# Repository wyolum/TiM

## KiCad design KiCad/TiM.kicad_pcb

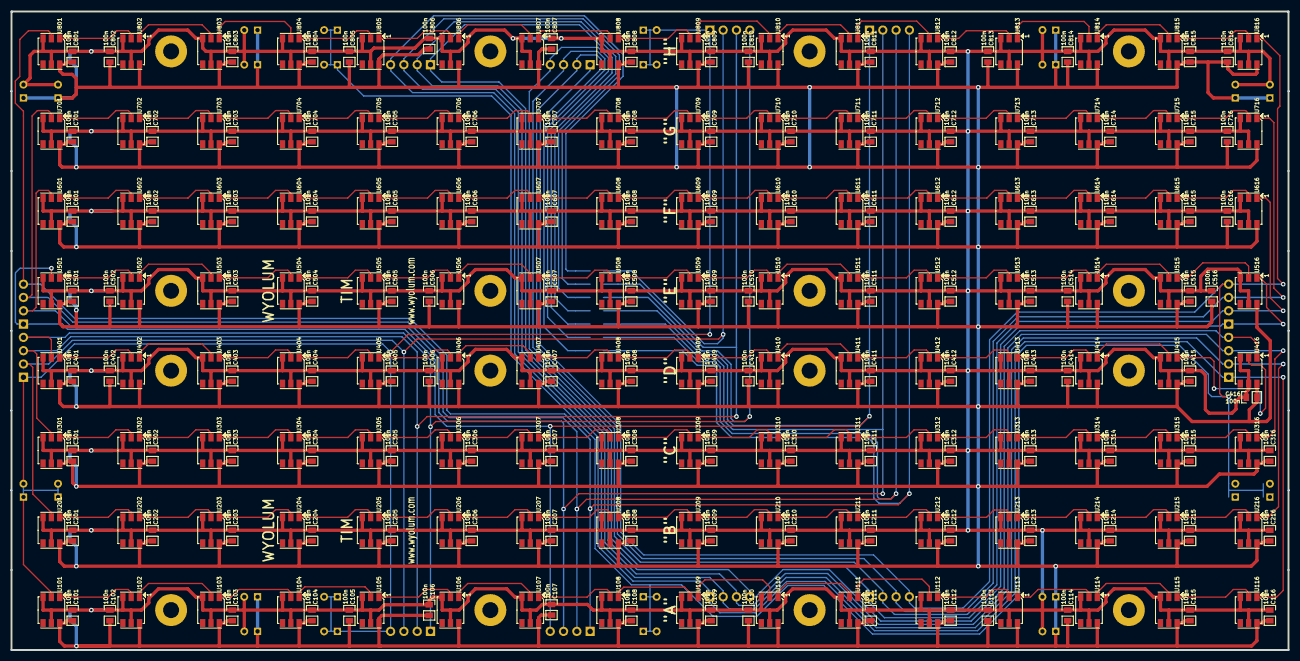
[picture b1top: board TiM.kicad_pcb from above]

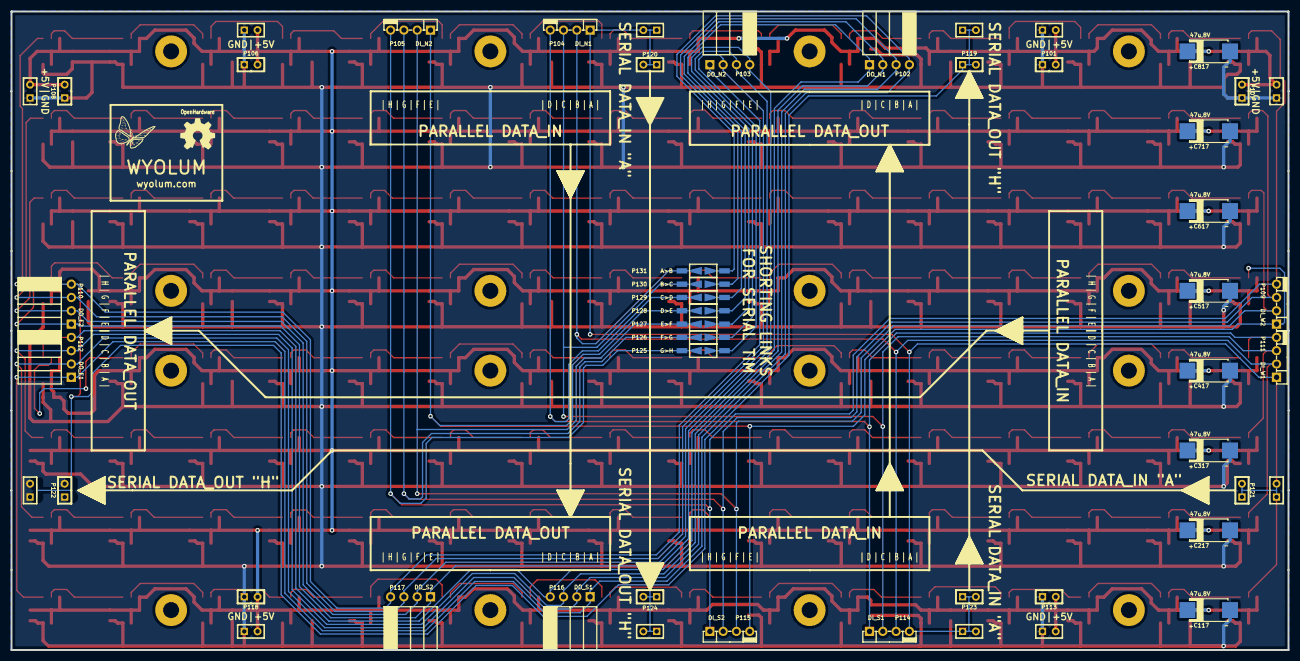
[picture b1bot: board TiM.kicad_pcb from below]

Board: 2 copper layers, 243.8 x 121.9 mm, 313 parts (41 on the bottom side), 138 nets.

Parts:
C101, C102, C103, C104, C105, C106, C107, C108, C109, C110, C111, C112, C113, C114, C115, C116, C201, C202, C203, C204, C205, C206, C207, C208, C209, C210, C211, C212, C213, C214, C215, C216, C301, C302, C303, C304, C305, C306, C307, C308, C309, C310, C311, C312, C313, C314, C315, C316, C401, C402, C403, C404, C405, C406, C407, C408, C409, C410, C411, C412, C413, C414, C415, C416, C501, C502, C503, C504, C505, C506, C507, C508, C509, C510, C511, C512, C513, C514, C515, C516, C601, C602, C603, C604, C605, C606, C607, C608, C609, C610, C611, C612, C613, C614, C615, C616, C701, C702, C703, C704, C705, C706, C707, C708, C709, C710, C711, C712, C713, C714, C715, C716, C801, C802, C803, C804, C805, C806, C807, C808, C809, C810, C811, C812, C813, C814, C815, C816: 100n; c_0805
C117, C217, C317, C417, C517, C617, C717, C817: 47u,8V; c_2917
L101: OSHW; OSHW_6mm
L102: Wyolum; Logo-WL3
P101: PWR_NW; SIL-PWR-2
P102: DO_N1; CONN_S
P103: DO_N2; CONN_S
P104: DI_N1; CONN_N
P105: DI_N2; CONN_N
P106: PWR_NE; SIL-PWR-2
P107: PWR_W; SIL-PWR
P108: PWR_E; SIL-PWR-2
P109: DI_W2; CONN_N
P110: DO_E2; CONN_S
P111: DI_W1; CONN_N
P112: DO_E1; CONN_S
P113: PWR_SW; SIL-PWR
P114: DI_S1; CONN_N
P115: DI_S2; CONN_N
P116: DO_S1; CONN_S
P117: DO_S2; CONN_S
P118: PWR_SE; SIL-PWR
P119, P122: DO_H_SER; SIL-PWR-2
P120, P121: DI_A_SER; SIL-PWR
P123: DI_A_Ser; SIL-PWR
P124: DO_H_Ser; SIL-PWR-2
P125: G>H; ShortLink2
P126: F>G; ShortLink2
P127: E>F; ShortLink2
P128: D>E; ShortLink2
P129: C>D; ShortLink2
P130: B>C; ShortLink2
P131: A>B; ShortLink2
S101, S102, S103, S104, S401, S402, S403, S404, S501, S502, S503, S504, S801, S802, S803, S804: CONN_1; Screw
U101, U102, U103, U104, U105, U106, U107, U108, U109, U110, U111, U112, U113, U114, U115, U116, U201, U202, U203, U204, U205, U206, U207, U208, U209, U210, U211, U212, U213, U214, U215, U216, U301, U302, U303, U304, U305, U306, U307, U308, U309, U310, U311, U312, U313, U314, U315, U316, U401, U402, U403, U404, U405, U406, U407, U408, U409, U410, U411, U412, U413, U414, U415, U416, U501, U502, U503, U504, U505, U506, U507, U508, U509, U510, U511, U512, U513, U514, U515, U516, U601, U602, U603, U604, U605, U606, U607, U608, U609, U610, U611, U612, U613, U614, U615, U616, U701, U702, U703, U704, U705, U706, U707, U708, U709, U710, U711, U712, U713, U714, U715, U716, U801, U802, U803, U804, U805, U806, U807, U808, U809, U810, U811, U812, U813, U814, U815, U816: RGB_WS2811

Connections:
5V: C101.2, C102.2, C103.2, C104.2, C105.2, C106.2, C107.2, C108.2, C109.2, C110.2, C111.2, C112.2, C113.2, C114.2, C115.2, C116.2, C117.1, C201.2, C202.2, C203.2, C204.2, C205.2, C206.2, C207.2, C208.2, C209.2, C210.2, C211.2, C212.2, C213.2, C214.2, C215.2, C216.2, C217.1, C301.2, C302.2, C303.2, C304.2, C305.2, C306.2, C307.2, C308.2, C309.2, C310.2, C311.2, C312.2, C313.2, C314.2, C315.2, C316.2, C317.1, C401.2, C402.2, C403.2, C404.2, C405.2, C406.2, C407.2, C408.2, C409.2, C410.2, C411.2, C412.2, C413.2, C414.2, C415.2, C416.2, C417.1, C501.2, C502.2, C503.2, C504.2, C505.2, C506.2, C507.2, C508.2, C509.2, C510.2, C511.2, C512.2, C513.2, C514.2, C515.2, C516.2, C517.1, C601.2, C602.2, C603.2, C604.2, C605.2, C606.2, C607.2, C608.2, C609.2, C610.2, C611.2, C612.2, C613.2, C614.2, C615.2, C616.2, C617.1, C701.2, C702.2, C703.2, C704.2, C705.2, C706.2, C707.2, C708.2, C709.2, C710.2, C711.2, C712.2, C713.2, C714.2, C715.2, C716.2, C717.1, C801.2, C802.2, C803.2, C804.2, C805.2, C806.2, C807.2, C808.2, C809.2, C810.2, C811.2, C812.2, C813.2, C814.2, C815.2, C816.2, C817.1, P101.1, P106.1, P107.1, P108.1, P113.1, P118.1, U101.3, U101.5, U102.3, U102.5, U103.3, U103.5, U104.3, U104.5, U105.3, U105.5, U106.3, U106.5, U107.3, U107.5, U108.3, U108.5, U109.3, U109.5, U110.3, U110.5, U111.3, U111.5, U112.3, U112.5, U113.3, U113.5, U114.3, U114.5, U115.3, U115.5, U116.3, U116.5, U201.3, U201.5, U202.3, U202.5, U203.3, U203.5, U204.3, U204.5, U205.3, U205.5, U206.3, U206.5, U207.3, U207.5, U208.3, U208.5, U209.3, U209.5, U210.3, U210.5, U211.3, U211.5, U212.3, U212.5, U213.3, U213.5, U214.3, U214.5, U215.3, U215.5, U216.3, U216.5, U301.3, U301.5, U302.3, U302.5, U303.3, U303.5, U304.3, U304.5, U305.3, U305.5, U306.3, U306.5, U307.3, U307.5, U308.3, U308.5, U309.3, U309.5, U310.3, U310.5, U311.3, U311.5, U312.3, U312.5, U313.3, U313.5, U314.3, U314.5, U315.3, U315.5, U316.3, U316.5, U401.3, U401.5, U402.3, U402.5, U403.3, U403.5, U404.3, U404.5, U405.3, U405.5, U406.3, U406.5, U407.3, U407.5, U408.3, U408.5, U409.3, U409.5, U410.3, U410.5, U411.3, U411.5, U412.3, U412.5, U413.3, U413.5, U414.3, U414.5, U415.3, U415.5, U416.3, U416.5, U501.3, U501.5, U502.3, U502.5, U503.3, U503.5, U504.3, U504.5, U505.3, U505.5, U506.3, U506.5, U507.3, U507.5, U508.3, U508.5, U509.3, U509.5, U510.3, U510.5, U511.3, U511.5, U512.3, U512.5, U513.3, U513.5, U514.3, U514.5, U515.3, U515.5, U516.3, U516.5, U601.3, U601.5, U602.3, U602.5, U603.3, U603.5, U604.3, U604.5, U605.3, U605.5, U606.3, U606.5, U607.3, U607.5, U608.3, U608.5, U609.3, U609.5, U610.3, U610.5, U611.3, U611.5, U612.3, U612.5, U613.3, U613.5, U614.3, U614.5, U615.3, U615.5, U616.3, U616.5, U701.3, U701.5, U702.3, U702.5, U703.3, U703.5, U704.3, U704.5, U705.3, U705.5, U706.3, U706.5, U707.3, U707.5, U708.3, U708.5, U709.3, U709.5, U710.3, U710.5, U711.3, U711.5, U712.3, U712.5, U713.3, U713.5, U714.3, U714.5, U715.3, U715.5, U716.3, U716.5, U801.3, U801.5, U802.3, U802.5, U803.3, U803.5, U804.3, U804.5, U805.3, U805.5, U806.3, U806.5, U807.3, U807.5, U808.3, U808.5, U809.3, U809.5, U810.3, U810.5, U811.3, U811.5, U812.3, U812.5, U813.3, U813.5, U814.3, U814.5, U815.3, U815.5, U816.3, U816.5
/Row_A/A_02: U101.1, U102.2
/Row_A/A_03: U102.1, U103.2
/Row_A/A_04: U103.1, U104.2
/Row_A/A_05: U104.1, U105.2
/Row_A/A_06: U105.1, U106.2
/Row_A/A_07: U106.1, U107.2
/Row_A/A_08: U107.1, U108.2
/Row_A/A_09: U108.1, U109.2
/Row_A/A_10: U109.1, U110.2
/Row_A/A_11: U110.1, U111.2
/Row_A/A_12: U111.1, U112.2
/Row_A/A_13: U112.1, U113.2
/Row_A/A_14: U113.1, U114.2
/Row_A/A_15: U114.1, U115.2
/Row_A/A_16: U115.1, U116.2
/Row_A/DI_A: P104.4, P111.4, P114.1, P120.1, P120.2, P121.1, P121.2, P123.1, P123.2, U101.2
/Row_A/DO_A: P102.1, P112.4, P116.4, P131.2, U116.1
/Row_B/B_02: U201.1, U202.2
/Row_B/B_03: U202.1, U203.2
/Row_B/B_04: U203.1, U204.2
/Row_B/B_05: U204.1, U205.2
/Row_B/B_06: U205.1, U206.2
/Row_B/B_07: U206.1, U207.2
/Row_B/B_08: U207.1, U208.2
/Row_B/B_09: U208.1, U209.2
/Row_B/B_10: U209.1, U210.2
/Row_B/B_11: U210.1, U211.2
/Row_B/B_12: U211.1, U212.2
/Row_B/B_13: U212.1, U213.2
/Row_B/B_14: U213.1, U214.2
/Row_B/B_15: U214.1, U215.2
/Row_B/B_16: U215.1, U216.2
/Row_B/DI_B: P104.3, P111.3, P114.2, P131.1, U201.2
/Row_B/DO_B: P102.2, P112.3, P116.3, P130.2, U216.1
/Row_C/C_02: U301.1, U302.2
/Row_C/C_03: U302.1, U303.2
/Row_C/C_04: U303.1, U304.2
/Row_C/C_05: U304.1, U305.2
/Row_C/C_06: U305.1, U306.2
/Row_C/C_07: U306.1, U307.2
/Row_C/C_08: U307.1, U308.2
/Row_C/C_09: U308.1, U309.2
/Row_C/C_10: U309.1, U310.2
/Row_C/C_11: U310.1, U311.2
/Row_C/C_12: U311.1, U312.2
/Row_C/C_13: U312.1, U313.2
/Row_C/C_14: U313.1, U314.2
/Row_C/C_15: U314.1, U315.2
/Row_C/C_16: U315.1, U316.2
/Row_C/DI_C: P104.2, P111.2, P114.3, P130.1, U301.2
/Row_C/DO_C: P102.3, P112.2, P116.2, P129.2, U316.1
/Row_D/DI_D: P104.1, P111.1, P114.4, P129.1, U401.2
/Row_D/DO_D: P102.4, P112.1, P116.1, P128.2, U416.1
/Row_D/D_02: U401.1, U402.2
/Row_D/D_03: U402.1, U403.2
/Row_D/D_04: U403.1, U404.2
/Row_D/D_05: U404.1, U405.2
/Row_D/D_06: U405.1, U406.2
/Row_D/D_07: U406.1, U407.2
/Row_D/D_08: U407.1, U408.2
/Row_D/D_09: U408.1, U409.2
/Row_D/D_10: U409.1, U410.2
/Row_D/D_11: U410.1, U411.2
/Row_D/D_12: U411.1, U412.2
/Row_D/D_13: U412.1, U413.2
/Row_D/D_14: U413.1, U414.2
/Row_D/D_15: U414.1, U415.2
/Row_D/D_16: U415.1, U416.2
/Row_E/DI_E: P105.4, P109.4, P115.1, P128.1, U501.2
/Row_E/DO_E: P103.1, P110.4, P117.4, P127.2, U516.1
/Row_E/E_02: U501.1, U502.2
/Row_E/E_03: U502.1, U503.2
/Row_E/E_04: U503.1, U504.2
/Row_E/E_05: U504.1, U505.2
/Row_E/E_06: U505.1, U506.2
/Row_E/E_07: U506.1, U507.2
/Row_E/E_08: U507.1, U508.2
/Row_E/E_09: U508.1, U509.2
/Row_E/E_10: U509.1, U510.2
/Row_E/E_11: U510.1, U511.2
/Row_E/E_12: U511.1, U512.2
/Row_E/E_13: U512.1, U513.2
/Row_E/E_14: U513.1, U514.2
/Row_E/E_15: U514.1, U515.2
/Row_E/E_16: U515.1, U516.2
/Row_F/DI_F: P105.3, P109.3, P115.2, P127.1, U601.2
/Row_F/DO_F: P103.2, P110.3, P117.3, P126.2, U616.1
/Row_F/F_02: U601.1, U602.2
/Row_F/F_03: U602.1, U603.2
/Row_F/F_04: U603.1, U604.2
/Row_F/F_05: U604.1, U605.2
/Row_F/F_06: U605.1, U606.2
/Row_F/F_07: U606.1, U607.2
/Row_F/F_08: U607.1, U608.2
/Row_F/F_09: U608.1, U609.2
/Row_F/F_10: U609.1, U610.2
/Row_F/F_11: U610.1, U611.2
/Row_F/F_12: U611.1, U612.2
/Row_F/F_13: U612.1, U613.2
/Row_F/F_14: U613.1, U614.2
/Row_F/F_15: U614.1, U615.2
/Row_F/F_16: U615.1, U616.2
/Row_G/DI_G: P105.2, P109.2, P115.3, P126.1, U701.2
/Row_G/DO_G: P103.3, P110.2, P117.2, P125.2, U716.1
/Row_G/G_02: U701.1, U702.2
/Row_G/G_03: U702.1, U703.2
/Row_G/G_04: U703.1, U704.2
/Row_G/G_05: U704.1, U705.2
/Row_G/G_06: U705.1, U706.2
/Row_G/G_07: U706.1, U707.2
/Row_G/G_08: U707.1, U708.2
/Row_G/G_09: U708.1, U709.2
/Row_G/G_10: U709.1, U710.2
/Row_G/G_11: U710.1, U711.2
/Row_G/G_12: U711.1, U712.2
/Row_G/G_13: U712.1, U713.2
/Row_G/G_14: U713.1, U714.2
/Row_G/G_15: U714.1, U715.2
/Row_G/G_16: U715.1, U716.2
/Row_H/DI_H: P105.1, P109.1, P115.4, P125.1, U801.2
/Row_H/DO_H: P103.4, P110.1, P117.1, P119.1, P119.2, P122.1, P122.2, P124.1, P124.2, U816.1
/Row_H/H_02: U801.1, U802.2
/Row_H/H_03: U802.1, U803.2
/Row_H/H_04: U803.1, U804.2
/Row_H/H_05: U804.1, U805.2
/Row_H/H_06: U805.1, U806.2
/Row_H/H_07: U806.1, U807.2
/Row_H/H_08: U807.1, U808.2
/Row_H/H_09: U808.1, U809.2
/Row_H/H_10: U809.1, U810.2
/Row_H/H_11: U810.1, U811.2
/Row_H/H_12: U811.1, U812.2
/Row_H/H_13: U812.1, U813.2
/Row_H/H_14: U813.1, U814.2
/Row_H/H_15: U814.1, U815.2
/Row_H/H_16: U815.1, U816.2
GND: C101.1, C102.1, C103.1, C104.1, C105.1, C106.1, C107.1, C108.1, C109.1, C110.1, C111.1, C112.1, C113.1, C114.1, C115.1, C116.1, C117.2, C201.1, C202.1, C203.1, C204.1, C205.1, C206.1, C207.1, C208.1, C209.1, C210.1, C211.1, C212.1, C213.1, C214.1, C215.1, C216.1, C217.2, C301.1, C302.1, C303.1, C304.1, C305.1, C306.1, C307.1, C308.1, C309.1, C310.1, C311.1, C312.1, C313.1, C314.1, C315.1, C316.1, C317.2, C401.1, C402.1, C403.1, C404.1, C405.1, C406.1, C407.1, C408.1, C409.1, C410.1, C411.1, C412.1, C413.1, C414.1, C415.1, C416.1, C417.2, C501.1, C502.1, C503.1, C504.1, C505.1, C506.1, C507.1, C508.1, C509.1, C510.1, C511.1, C512.1, C513.1, C514.1, C515.1, C516.1, C517.2, C601.1, C602.1, C603.1, C604.1, C605.1, C606.1, C607.1, C608.1, C609.1, C610.1, C611.1, C612.1, C613.1, C614.1, C615.1, C616.1, C617.2, C701.1, C702.1, C703.1, C704.1, C705.1, C706.1, C707.1, C708.1, C709.1, C710.1, C711.1, C712.1, C713.1, C714.1, C715.1, C716.1, C717.2, C801.1, C802.1, C803.1, C804.1, C805.1, C806.1, C807.1, C808.1, C809.1, C810.1, C811.1, C812.1, C813.1, C814.1, C815.1, C816.1, C817.2, P101.2, P106.2, P107.2, P108.2, P113.2, P118.2, U101.6, U102.6, U103.6, U104.6, U105.6, U106.6, U107.6, U108.6, U109.6, U110.6, U111.6, U112.6, U113.6, U114.6, U115.6, U116.6, U201.6, U202.6, U203.6, U204.6, U205.6, U206.6, U207.6, U208.6, U209.6, U210.6, U211.6, U212.6, U213.6, U214.6, U215.6, U216.6, U301.6, U302.6, U303.6, U304.6, U305.6, U306.6, U307.6, U308.6, U309.6, U310.6, U311.6, U312.6, U313.6, U314.6, U315.6, U316.6, U401.6, U402.6, U403.6, U404.6, U405.6, U406.6, U407.6, U408.6, U409.6, U410.6, U411.6, U412.6, U413.6, U414.6, U415.6, U416.6, U501.6, U502.6, U503.6, U504.6, U505.6, U506.6, U507.6, U508.6, U509.6, U510.6, U511.6, U512.6, U513.6, U514.6, U515.6, U516.6, U601.6, U602.6, U603.6, U604.6, U605.6, U606.6, U607.6, U608.6, U609.6, U610.6, U611.6, U612.6, U613.6, U614.6, U615.6, U616.6, U701.6, U702.6, U703.6, U704.6, U705.6, U706.6, U707.6, U708.6, U709.6, U710.6, U711.6, U712.6, U713.6, U714.6, U715.6, U716.6, U801.6, U802.6, U803.6, U804.6, U805.6, U806.6, U807.6, U808.6, U809.6, U810.6, U811.6, U812.6, U813.6, U814.6, U815.6, U816.6

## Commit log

2013-05-27 Clean up dir, PyStream working
2013-05-27 Clean up directory
2013-05-28 ssh testing
2013-06-23 added pygame example
2013-06-23 configured matris for pi
2013-06-29 modified cksum
2013-06-29 merged changes
2013-06-30 debugging in pi
2013-06-30 made major changes to input stream on alamode so that it works with rpi
2013-06-30 created TiM.Surface class for automatic pygame incorporation
2013-06-30 added yellow_snack example
2013-06-30 got yellow snake to run
2013-07-01 playing with snake
2013-07-01 added gradient pattern
2013-07-02 made changes so it works with both pi and ftdi
2013-07-05 minor tweaks
2013-07-13 added color balancing matrix
2013-11-01 Cleaned up Random example
2013-11-01 Swapped N_ROW/N_COL
2013-11-08 added a comment
2014-02-17 added Screen.ino
2014-02-17 added Ankit's mods: set/clearRow()
2014-03-22 updated NeoPixel lib with get/set/clear row
2014-04-19 added KiCad project files to Github. Single row - RowGB - and matrix TiM
2014-08-08 added fabricate folder with 3d printable scrabble tiles, experimental for face plate
2014-12-19 modified test code
2014-12-19 added neo pixel lib
2016-03-24 building a Mood Lamp, in faricate directory
2016-04-03 added TiM Mood lighting app
2016-04-03 added comments to TiMood
2016-04-03 added a comment to TiMood
2016-04-05 single pot, modular moodlight
2016-04-06 add GFX and matrix libraries
2016-04-06 match anool's config
2016-04-07 modified scrolling texty.h to include two TiM boards for a 16x16 matrix
2016-04-17 changed pin configs to match Anool's MoodLight wiring
